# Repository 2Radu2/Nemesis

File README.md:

# Project Nemesis: Modular Wireless Auditor

## Legal Disclaimer
**This project is for educational and academic research purposes only.**

Project Nemesis was developed as a university thesis project to audit, stress-test, and evaluate the resilience of modern wireless protocols (IEEE 802.11 and Bluetooth) in strictly controlled and isolated laboratory environments.

The author does not endorse, encourage, or take responsibility for any illegal, malicious, or unauthorized use of this hardware or software. Transmitting jamming signals or executing deauthentication attacks against networks or devices without explicit, written permission from the network owner is a federal crime in many jurisdictions (including under FCC regulations in the United States and similar laws worldwide).

By downloading, viewing, or building this project, you agree that you are solely responsible for your own actions and that you will comply with all local, state, and federal laws.

---

##  Overview
Project Nemesis is a portable, offensive security embedded system designed to audit and stress-test the resilience of modern wireless networks (Wi-Fi & Bluetooth).

Unlike standard auditing tools that rely on a single microcontroller (which often leads to severe UI lag and firmware bottlenecks during heavy RF injection), this project utilizes a custom **3-Stack Hardware Architecture**:
- **Layer 1 (Master Controller):** An ESP32-S3 handling the TFT UI, joystick navigation, and SD-Card GPS logging, completely isolated from RF tasks to ensure zero UI lag.
- **Layer 2 (Bluetooth Disruption):** An ESP32-32U paired with a Quad-nRF24L01+PA+LNA array. It executes protocol-level BLE advertising floods and brute-force AFH (Adaptive Frequency Hopping) poisoning across 79 channels.
- **Layer 3 (Wi-Fi Attacker):** An ESP8266 utilizing the raw Espressif SDK to execute 802.11 deauthentication and beacon spam attacks.

By synchronizing these independent layers, the system can execute "Combo Max"—a simultaneous, multi-vector attack capable of completely saturating the 2.4 GHz spectrum while maintaining a perfectly fluid user interface.

##  Hardware Components
This project relies on a custom 3-stack PCB architecture to distribute processing power and prevent UI bottlenecks. Below is the full bill of materials (BOM):

### Layer 1: Master Controller & UI
*   **Microcontroller:** ESP32-S3 (Dev Module)
*   **Display:** SPI TFT LCD Screen (e.g., ILI9341)
*   **Input:** 5-Pin Analog/Digital Joystick Module
*   **Telemetry:** GPS Module (u-blox NEO-6M / 7M)
*   **Storage:** MicroSD Card Adapter (SPI) + MicroSD Card

### Layer 2: Bluetooth Jammer
*   **Microcontroller:** ESP32-WROOM-32U (with U.FL connector for external BLE antenna)
*   **RF Array:** 4x nRF24L01+PA+LNA Transceiver Modules
*   **Antennas:** 5x 2.4GHz SMA Antennas (4 for NRF modules, 1 for ESP32 BLE)
*   **Power Smoothing:** 4x 10µF - 100µF Capacitors (essential for NRF module power stability)

### Layer 3: Wi-Fi Attacker
*   **Microcontroller:** ESP8266 (NodeMCU / Wemos D1 Mini)

### Power Delivery & PCB
*   **Battery:** 2500mAh Li-Po Battery (must support high current discharge ~1A+)
*   **Power Regulation:** High-current 3.3V and 5V Voltage Regulators
*   **Custom PCBs:** 3x Custom-designed Gerber boards (included in the /Hardware folder)

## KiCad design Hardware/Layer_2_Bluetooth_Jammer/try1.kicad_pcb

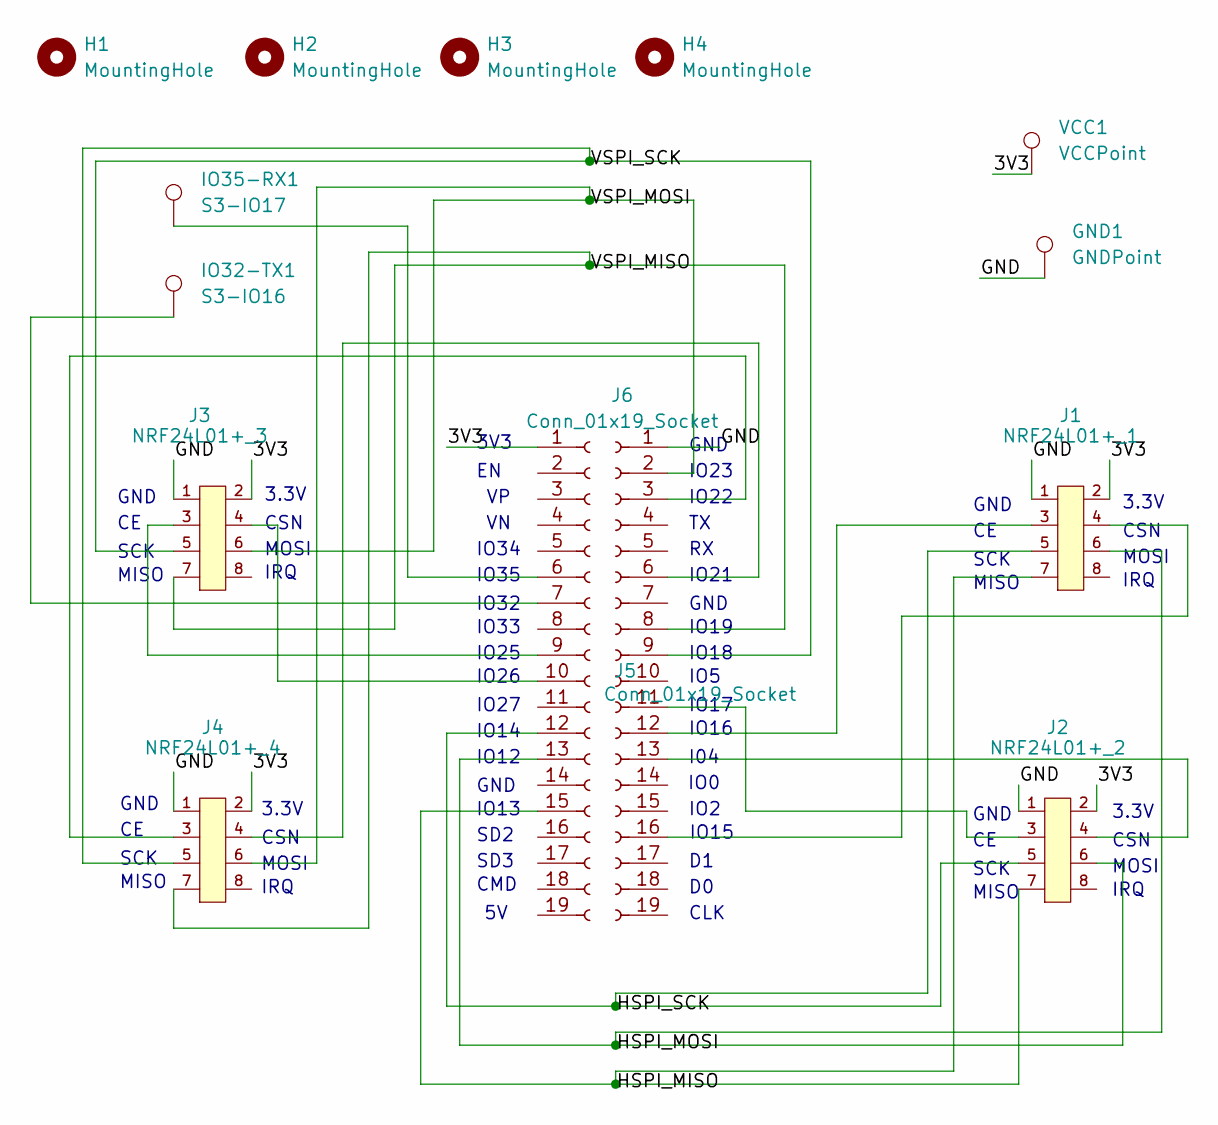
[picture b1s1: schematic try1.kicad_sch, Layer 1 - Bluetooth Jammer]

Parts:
GND1: GNDPoint; PinSocket_1x01_P2.54mm_Vertical
H1, H2, H3, H4: MountingHole; MountingHole_4.3mm_M4
IO32-TX1: S3-IO16; PinSocket_1x01_P2.54mm_Vertical
IO35-RX1: S3-IO17; PinSocket_1x01_P2.54mm_Vertical
J1: NRF24L01+_1; PinSocket_2x04_P2.54mm_Vertical
J2: NRF24L01+_2; PinSocket_2x04_P2.54mm_Vertical
J3: NRF24L01+_3; PinSocket_2x04_P2.54mm_Vertical
J4: NRF24L01+_4; PinSocket_2x04_P2.54mm_Vertical
J5, J6: Conn_01x19_Socket; PinSocket_1x19_P2.54mm_Vertical
VCC1: VCCPoint; PinSocket_1x01_P2.54mm_Vertical

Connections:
/3V3: J1.2 (VCC), J2.2 (VCC), J3.2 (VCC), J4.2 (VCC), J5.1, VCC1.1 (1_1)
/GND: GND1.1 (1_1), J1.1 (GND), J2.1 (GND), J3.1 (GND), J4.1 (GND), J6.1
/HSPI_MISO: J1.7 (MISO), J2.7 (MISO), J5.15
/HSPI_MOSI: J1.6 (MOSI), J2.6 (MOSI), J5.13
/HSPI_SCK: J1.5 (SCK), J2.5 (SCK), J5.12
/VSPI_MISO: J3.7 (MISO), J4.7 (MISO), J6.8
/VSPI_MOSI: J3.6 (MOSI), J4.6 (MOSI), J6.2
/VSPI_SCK: J3.5 (SCK), J4.5 (SCK), J6.9
unnamed: J1.3 (CE), J6.12
unnamed: J1.4 (CSN), J6.16
unnamed: J2.3 (CE), J6.11
unnamed: J2.4 (CSN), J6.13
unnamed: J3.3 (CE), J5.9
unnamed: J3.4 (CSN), J5.10
unnamed: J4.3 (CE), J6.3
unnamed: J4.4 (CSN), J6.6
unnamed: IO35-RX1.1 (1_1), J5.6
unnamed: IO32-TX1.1 (1_1), J5.7

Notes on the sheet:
MOSI
IO21
IO27
SCK
IO19
3.3V
IO14
SD3
I04
IO17
GND
IO2
3V3
IO23
IO16
CSN
MISO
GND
IO0
CLK
CMD
IO18
IO32
IO5
IO15
IO34
IO12
IO13
IRQ
IO35
IO33
IO26
IO22
IO25
SD2

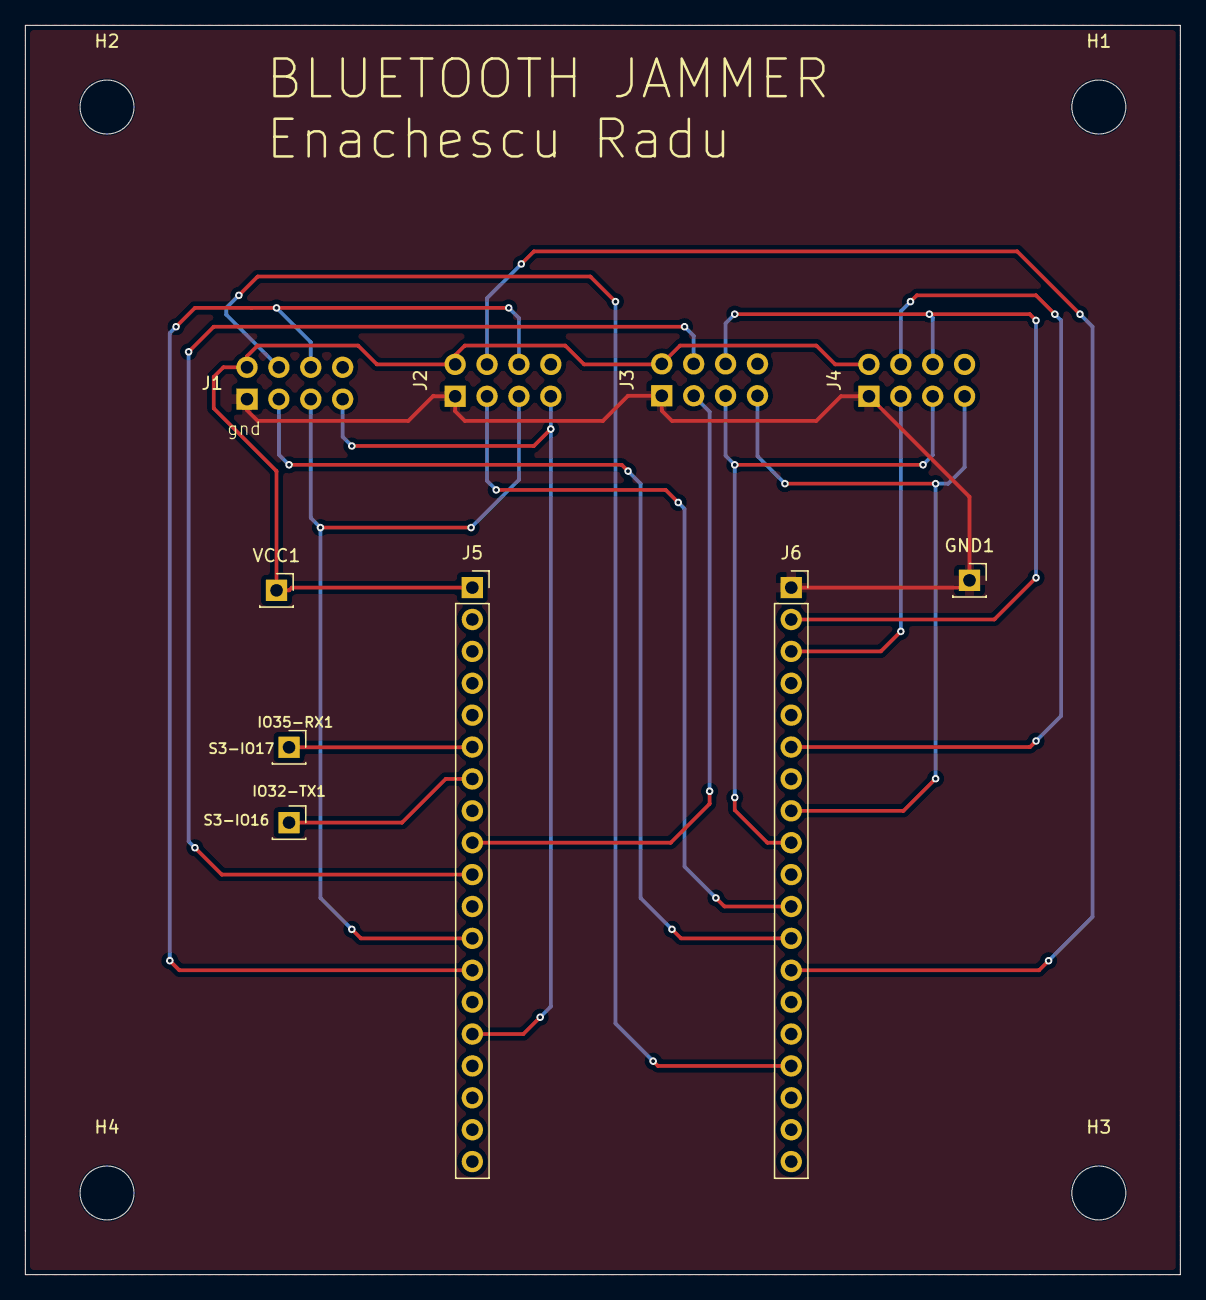
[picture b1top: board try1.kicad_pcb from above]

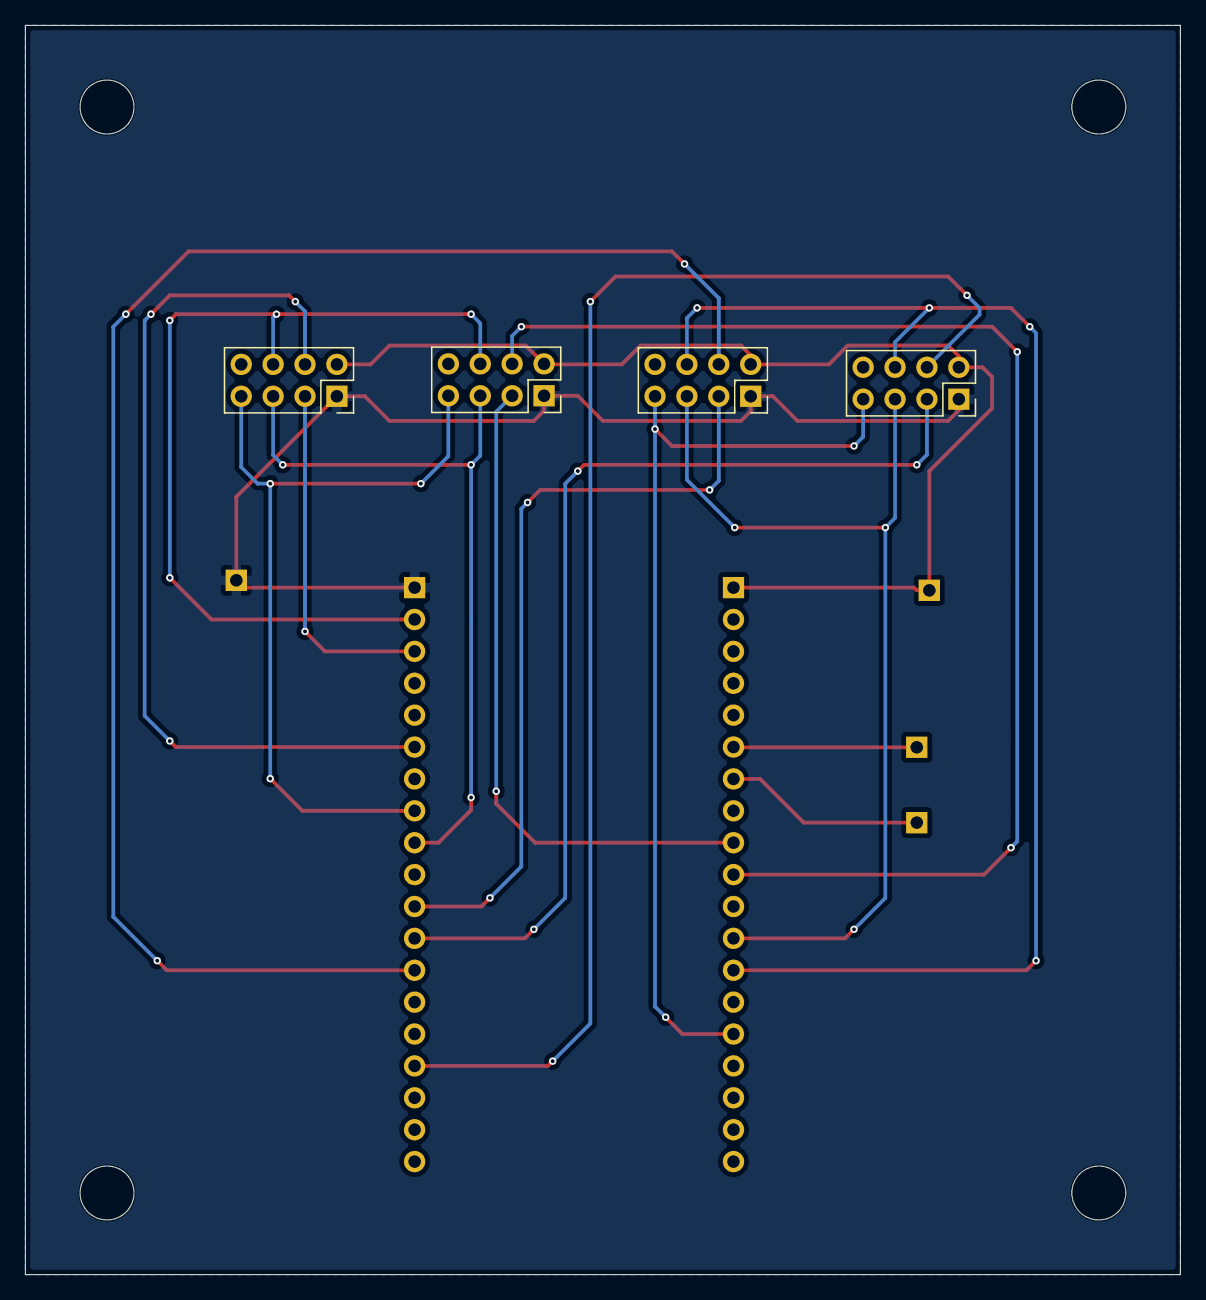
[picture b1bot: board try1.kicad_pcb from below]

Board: 2 copper layers, 92.0 x 99.5 mm, 14 parts (4 on the bottom side), 18 nets.

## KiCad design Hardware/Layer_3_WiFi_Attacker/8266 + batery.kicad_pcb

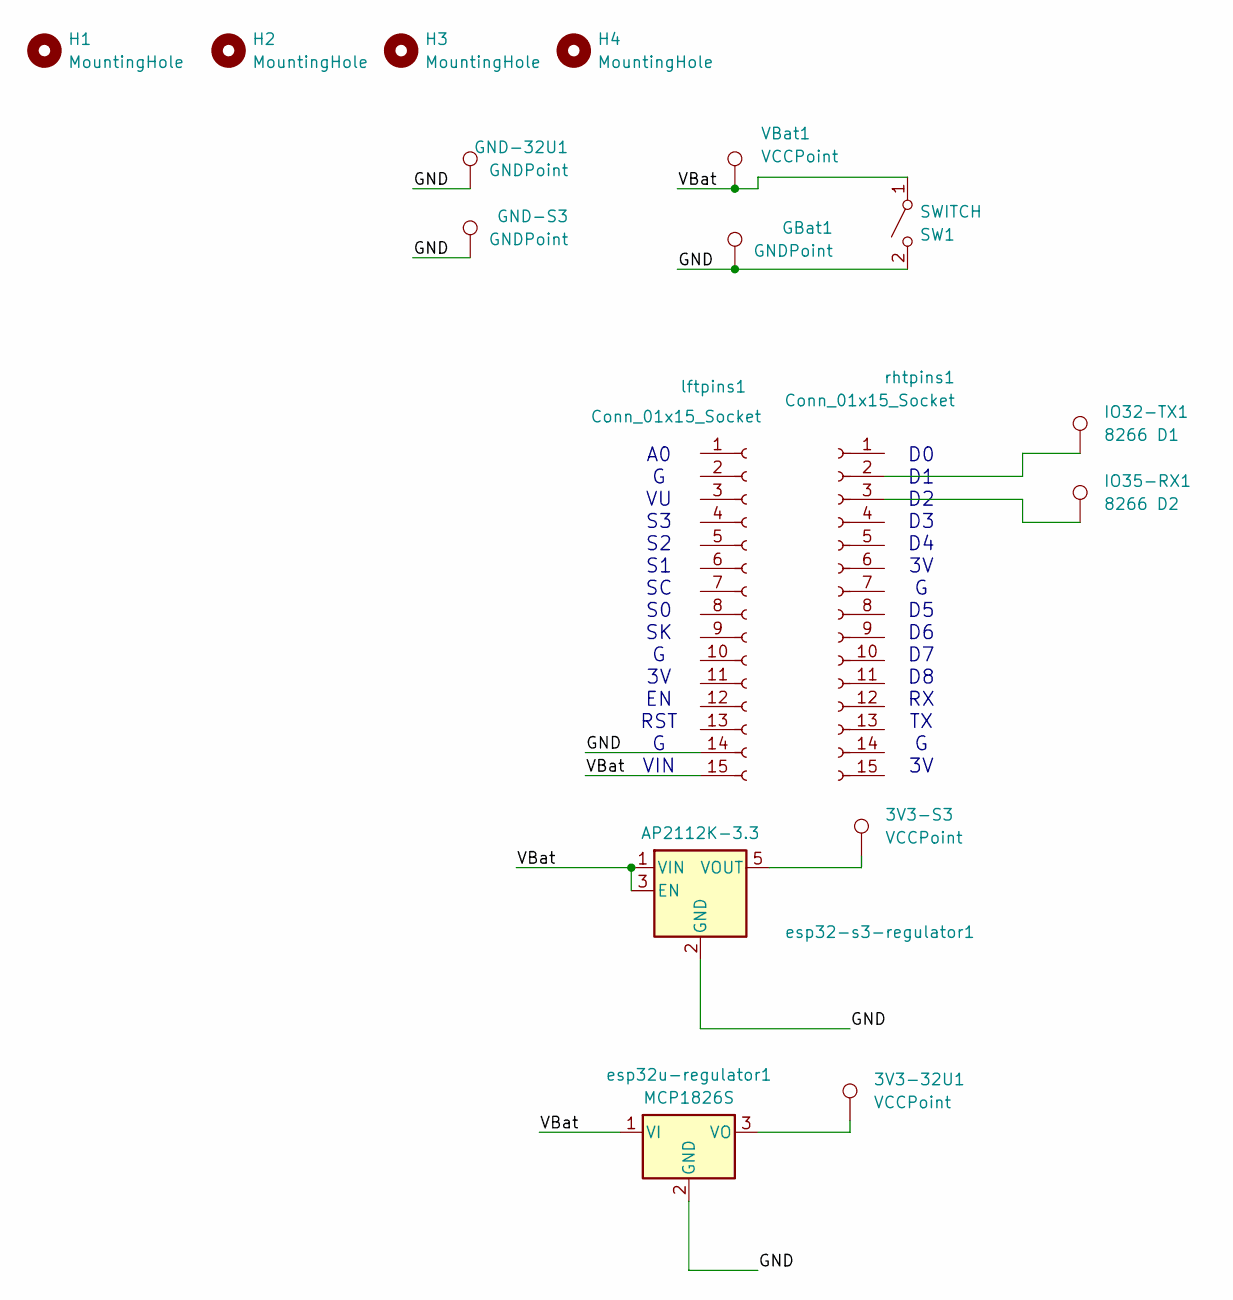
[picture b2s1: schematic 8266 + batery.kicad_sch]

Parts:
3V3-32U1, 3V3-S3: VCCPoint; PinSocket_1x01_P2.54mm_Vertical
GBat1: GNDPoint; PinSocket_1x01_P2.54mm_Vertical
GND-32U1: GNDPoint; PinSocket_1x01_P2.54mm_Vertical
GND-S3: GNDPoint; PinSocket_1x01_P2.54mm_Vertical
H1, H2, H3, H4: MountingHole; MountingHole_4.3mm_M4
IO32-TX1: 8266 D1; PinSocket_1x01_P2.54mm_Vertical
IO35-RX1: 8266 D2; PinSocket_1x01_P2.54mm_Vertical
SW1: SWITCH; PinHeader_1x02_P2.54mm_Vertical
VBat1: VCCPoint; PinSocket_1x01_P2.54mm_Vertical
esp32-s3-regulator1: AP2112K-3.3; SOT-23-5
esp32u-regulator1: MCP1826S; SOT-223-3_TabPin2
lftpins1: Conn_01x15_Socket; PinSocket_1x15_P2.54mm_Vertical
rhtpins1: Conn_01x15_Socket; PinSocket_1x15_P2.54mm_Vertical

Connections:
/GND: GBat1.1 (1_1), GND-32U1.1 (1_1), GND-S3.1 (1_1), SW1.2 (B), esp32-s3-regulator1.2 (GND), esp32u-regulator1.2 (GND), lftpins1.14
/VBat: SW1.1 (A), VBat1.1 (1_1), esp32-s3-regulator1.1 (VIN), esp32-s3-regulator1.3 (EN), esp32u-regulator1.1 (VI), lftpins1.15
unnamed: 3V3-S3.1 (1_1), esp32-s3-regulator1.5 (VOUT)
unnamed: 3V3-32U1.1 (1_1), esp32u-regulator1.3 (VO)
unnamed: IO32-TX1.1 (1_1), rhtpins1.2
unnamed: IO35-RX1.1 (1_1), rhtpins1.3

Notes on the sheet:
A0 G VU S3 S2 S1 SC S0 SK G 3V EN RST G VIN
D0 D1 D2 D3 D4 3V G D5 D6 D7 D8 RX TX G 3V

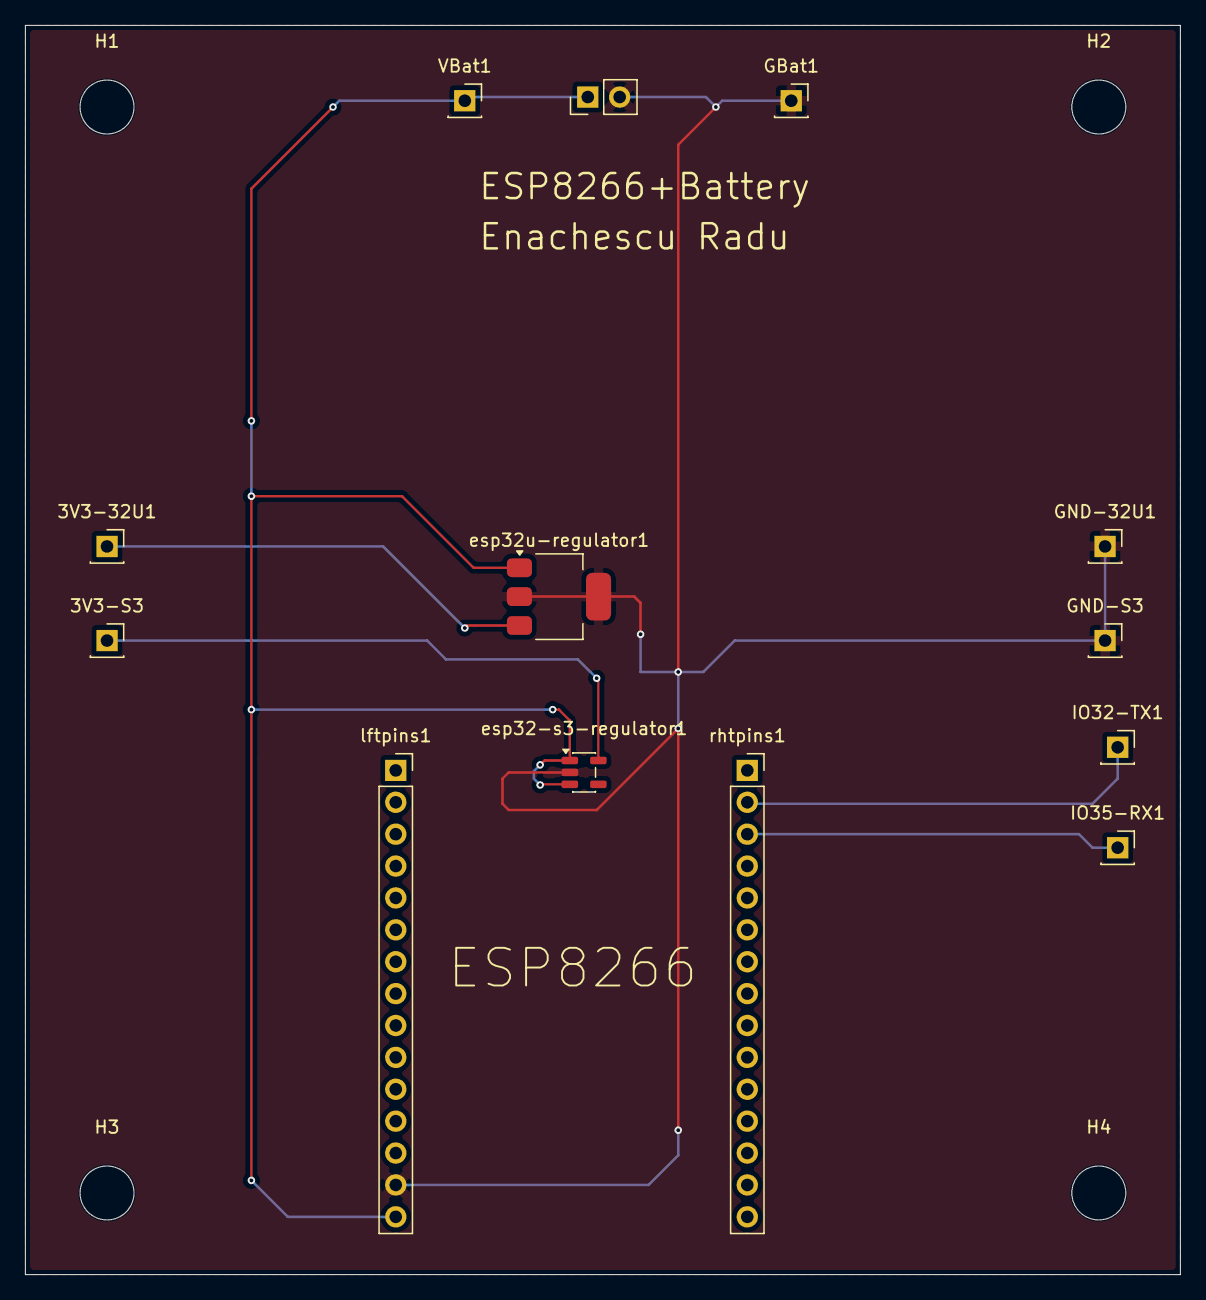
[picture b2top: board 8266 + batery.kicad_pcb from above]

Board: 2 copper layers, 92.0 x 99.5 mm, 17 parts (0 on the bottom side), 6 nets.

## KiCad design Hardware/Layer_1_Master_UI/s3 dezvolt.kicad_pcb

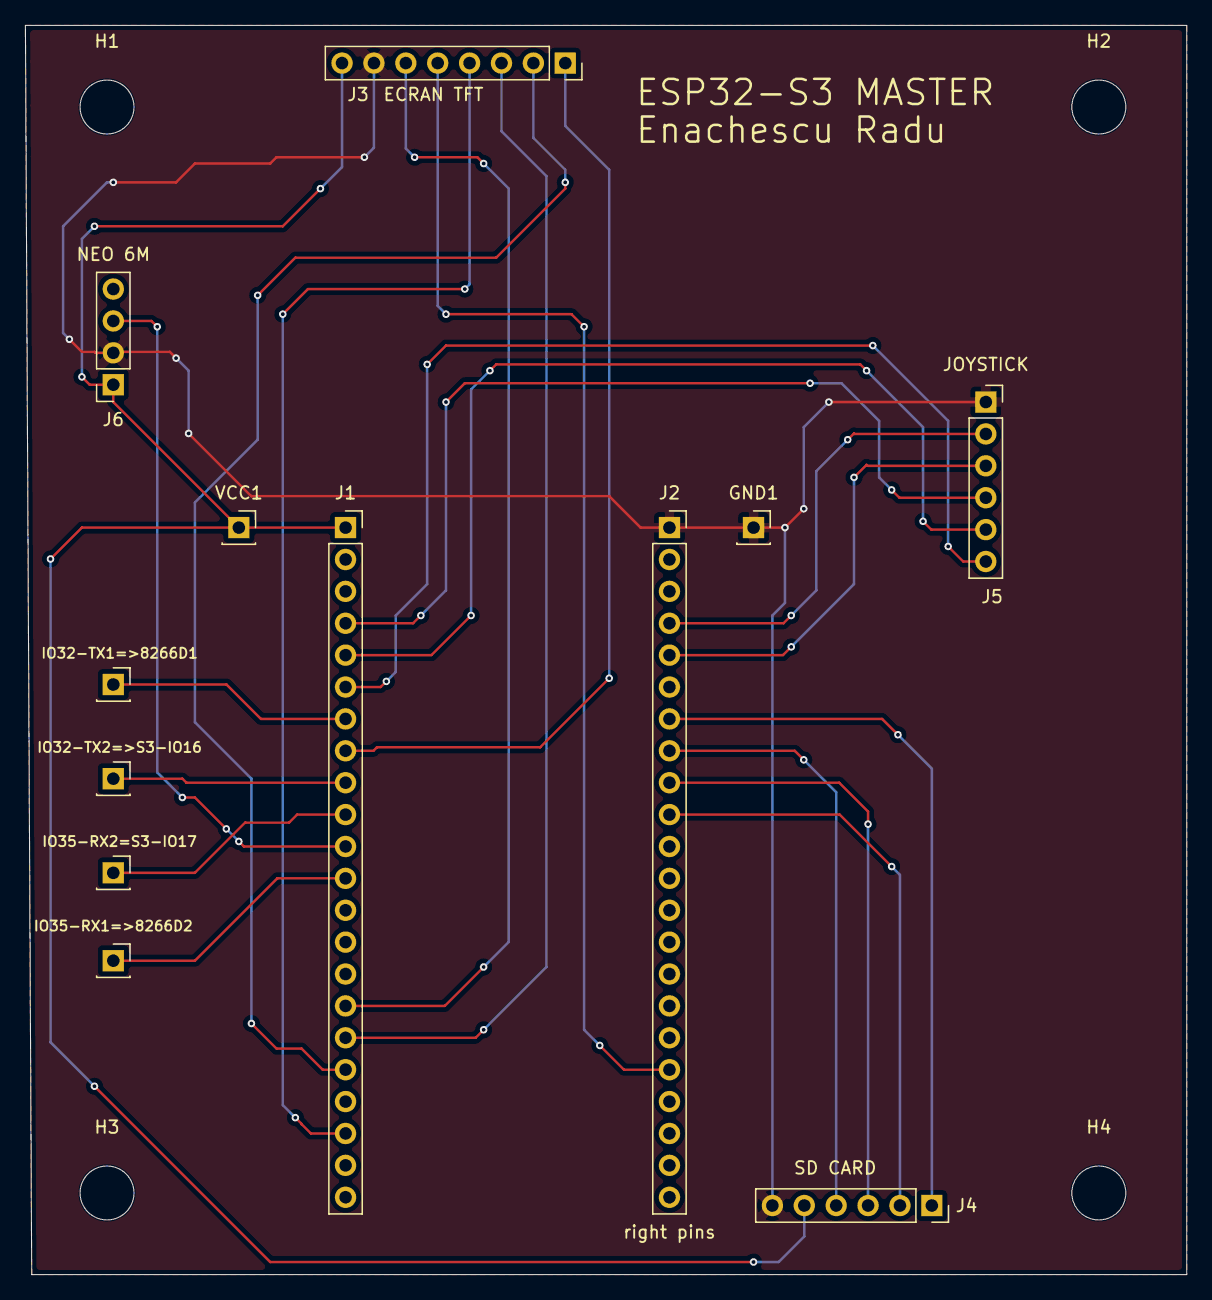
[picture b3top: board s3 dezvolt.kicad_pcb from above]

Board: 2 copper layers, 92.5 x 99.5 mm, 16 parts (0 on the bottom side), 22 nets.

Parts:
GND1: GNDPoint; PinSocket_1x01_P2.54mm_Vertical
H1, H2, H3, H4: MountingHole; MountingHole_4.3mm_M4
IO32-TX1=>8266D1: 8266 D1; PinSocket_1x01_P2.54mm_Vertical
IO32-TX2=>S3-IO16: S3-IO16; PinSocket_1x01_P2.54mm_Vertical
IO35-RX1=>8266D2: 8266 D2; PinSocket_1x01_P2.54mm_Vertical
IO35-RX2=S3-IO17: S3-IO17; PinSocket_1x01_P2.54mm_Vertical
J1: left pins; PinSocket_1x22_P2.54mm_Vertical
J2: right pins; PinSocket_1x22_P2.54mm_Vertical
J3: ECRAN TFT; PinSocket_1x08_P2.54mm_Vertical
J4: SD CARD; PinSocket_1x06_P2.54mm_Vertical
J5: JOYSTICK; PinSocket_1x06_P2.54mm_Vertical
J6: NEO 6M; PinSocket_1x04_P2.54mm_Vertical
VCC1: VCCPoint; PinSocket_1x01_P2.54mm_Vertical

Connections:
/3V3: J1.1, J3.8, J4.5, J6.1, VCC1.1 (1_1)
/GND: GND1.1 (1_1), J2.1, J3.7, J4.6, J5.1, J6.2
unnamed: J1.4, J5.4
unnamed: J1.5, J5.5
unnamed: J1.6, J5.6
unnamed: IO32-TX1=>8266D1.1 (1_1), J1.7
unnamed: J1.8, J3.1
unnamed: IO32-TX2=>S3-IO16.1 (1_1), J1.9
unnamed: IO35-RX2=S3-IO17.1 (1_1), J1.10
unnamed: J1.11, J6.3
unnamed: IO35-RX1=>8266D2.1 (1_1), J1.12
unnamed: J1.16, J3.6
unnamed: J1.17, J3.3
unnamed: J1.18, J3.2
unnamed: J1.20, J3.4
unnamed: J2.4, J5.2
unnamed: J2.5, J5.3
unnamed: J2.7, J4.1
unnamed: J2.8, J4.4
unnamed: J2.9, J4.3
unnamed: J2.10, J4.2
unnamed: J2.18, J3.5

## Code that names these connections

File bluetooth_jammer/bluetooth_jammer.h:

// bluetooth_jammer.h
// QUAD-NRF Bluetooth Jammer V8 (4× Firehose)
// 4× NRF24L01+ PA+LNA (+20dBm) + ESP32 BLE (+9dBm)
// ESP8266 WiFi attacks via Serial bridge
// Educational purposes only - jamming is ILLEGAL!

#ifndef BLUETOOTH_JAMMER_H
#define BLUETOOTH_JAMMER_H

#include <Arduino.h>
#include <SPI.h>
#include <RF24.h>

// ============================================================
// Hardware Pin Definitions
// ============================================================

// Number of NRF modules
#define NUM_NRFS        4

// NRF #1 — HSPI bus
#define NRF1_CE_PIN     16
#define NRF1_CSN_PIN    15

// NRF #2 — HSPI bus (shared SCK/MOSI/MISO with NRF #1)
#define NRF2_CE_PIN     17
#define NRF2_CSN_PIN    4

// NRF #3 — VSPI bus
#define NRF3_CE_PIN     25
#define NRF3_CSN_PIN    26

// NRF #4 — VSPI bus (shared SCK/MOSI/MISO with NRF #3)
#define NRF4_CE_PIN     22
#define NRF4_CSN_PIN    21

// HSPI signal pins (NRF #1, #2)
#define HSPI_SCK        14
#define HSPI_MOSI       12    // PCB routes NRF MOSI (pin 6) to GPIO12
#define HSPI_MISO       13    // PCB routes NRF MISO (pin 7) to GPIO13

// VSPI signal pins (NRF #3, #4)
#define VSPI_SCK        18
#define VSPI_MOSI       23
#define VSPI_MISO       19

// ESP8266 Serial bridge (for WiFi deauther commands)
#define ESP8266_TX_PIN  32    // ESP32 TX → ESP8266 RX
#define ESP8266_RX_PIN  35    // ESP32 RX ← ESP8266 TX (input-only pin)
#define ESP8266_BAUD    9600

// GPS Module (moved from GPIO16 to avoid NRF conflict)
#define GPS_RX_PIN      34    // ESP32 RX ← GPS TX (input-only pin)
#define GPS_BAUD        9600

// ============================================================
// Firehose parameters
// ============================================================

// Packets to blast on each channel before hopping.
// More = higher duty per channel but slower hopping.
// For BLE ADV (3 ch): lots of packets = high duty cycle
// For Classic BT (79 ch): more packets = stronger per-channel saturation
#define PKTS_PER_CH_FEW    50    // For 3-14 channel modes
#define PKTS_PER_CH_MANY   15    // For 40+ channel modes (higher dwell = more disruption)

// Burst-fire: packets per update() call
// NRF24 has 3-level TX FIFO — keep it saturated
#define BURST_COUNT        4

// Number of pre-generated noise patterns
#define NUM_NOISE_BUFS     8

// Regenerate noise buffers every N group rotations
// Prevents receiver from adapting to repeating patterns
#define NOISE_REGEN_CYCLES 50

// ============================================================
// Channel group rotation (AFH countermeasure)
// ============================================================
#define GROUP_SIZE         10     // Channels per focus group (concentrated fire works best)
#define GROUP_ROTATE_MS    2000   // Rotate every 2s (faster than AFH reclassify ~1-2s)

// Auto-cycle WITHOUT pause: shift group every 15s, never stop TX
// The group shift causes the "interrupt" effect at cycle start
// but we NEVER stop transmitting
#define CYCLE_ON_MS        10000  // Shift group every 10 seconds
#define CYCLE_OFF_MS       0      // NO pause — continuous TX

// ============================================================
// Jamming modes
// ============================================================
enum JamMode {
  JAM_BLUETOOTH,
  JAM_BLE,
  JAM_BLE_ADV_ONLY,
  JAM_WIFI,
  JAM_ALL,
  JAM_COMBO
};

// ============================================================
// Single NRF24L01+ Radio Instance
// ============================================================
class NRFRadio {
public:
  NRFRadio();
  bool init(SPIClass* spi, uint8_t cePin, uint8_t csnPin, int radioId);
  void startJamming(uint8_t* channels, uint8_t count, uint8_t pktsPerCh);
  void updateChannels(uint8_t* channels, uint8_t count);  // Lightweight swap (no restart)
  void stopJamming();
  void update();  // Blast packets + hop (burst-fire)
  void regenerateNoise();  // Refresh noise buffers (called periodically)

  bool isJamming();
  bool isInitialized();
  unsigned long getPacketsSent();
  unsigned long getHopsPerformed();
  int getId();

private:
  RF24 radio;
  int id;
  bool initialized;
  bool jamming;

  // Channel management
  uint8_t* channelList;
  uint8_t channelCount;
  uint8_t currentChannelIndex;
  uint8_t pktsPerChannel;
  uint8_t pktsSentOnChannel;

  // Stats
  unsigned long packetsSent;
  unsigned long hopsPerformed;

  // Noise buffers
  uint8_t noiseBuffers[NUM_NOISE_BUFS][32];
};

// ============================================================
// Multi-NRF Orchestrator (manages all 4 radios)
// ============================================================
class MultiNRFJammer {
public:
  MultiNRFJammer();
  bool init();
  void startJamming(JamMode mode);
  void stopJamming();
  void update();  // Round-robin update all radios

  bool isJamming();
  bool isInitialized();
  JamMode getMode();
  const char* getModeName();
  unsigned long getTotalPacketsSent();
  unsigned long getTotalHops();
  unsigned long getCycleCount();
  int getActiveRadioCount();

private:
  NRFRadio radios[NUM_NRFS];
  SPIClass* hspi;
  SPIClass* vspi;
  bool initialized;
  bool jamming;
  JamMode currentMode;
  int activeRadios;      // How many NRFs actually initialized
  int updateIndex;       // Round-robin counter

  // Cycling
  unsigned long cycleCount;
  unsigned long cycleStartMs;
  bool firstDivide;      // True on first call (use startJamming)

  // Cumulative counters (survive rotation resets)
  unsigned long cumulativePackets;
  unsigned long cumulativeHops;

  void divideChannels(JamMode mode);
};

// ============================================================
// ESP32 BLE Advertising Flood
// ============================================================
namespace ESP32BLEFlood {
  bool init();
  void start();
  void stop();
  void refreshData();
  bool isRunning();
}

#endif
